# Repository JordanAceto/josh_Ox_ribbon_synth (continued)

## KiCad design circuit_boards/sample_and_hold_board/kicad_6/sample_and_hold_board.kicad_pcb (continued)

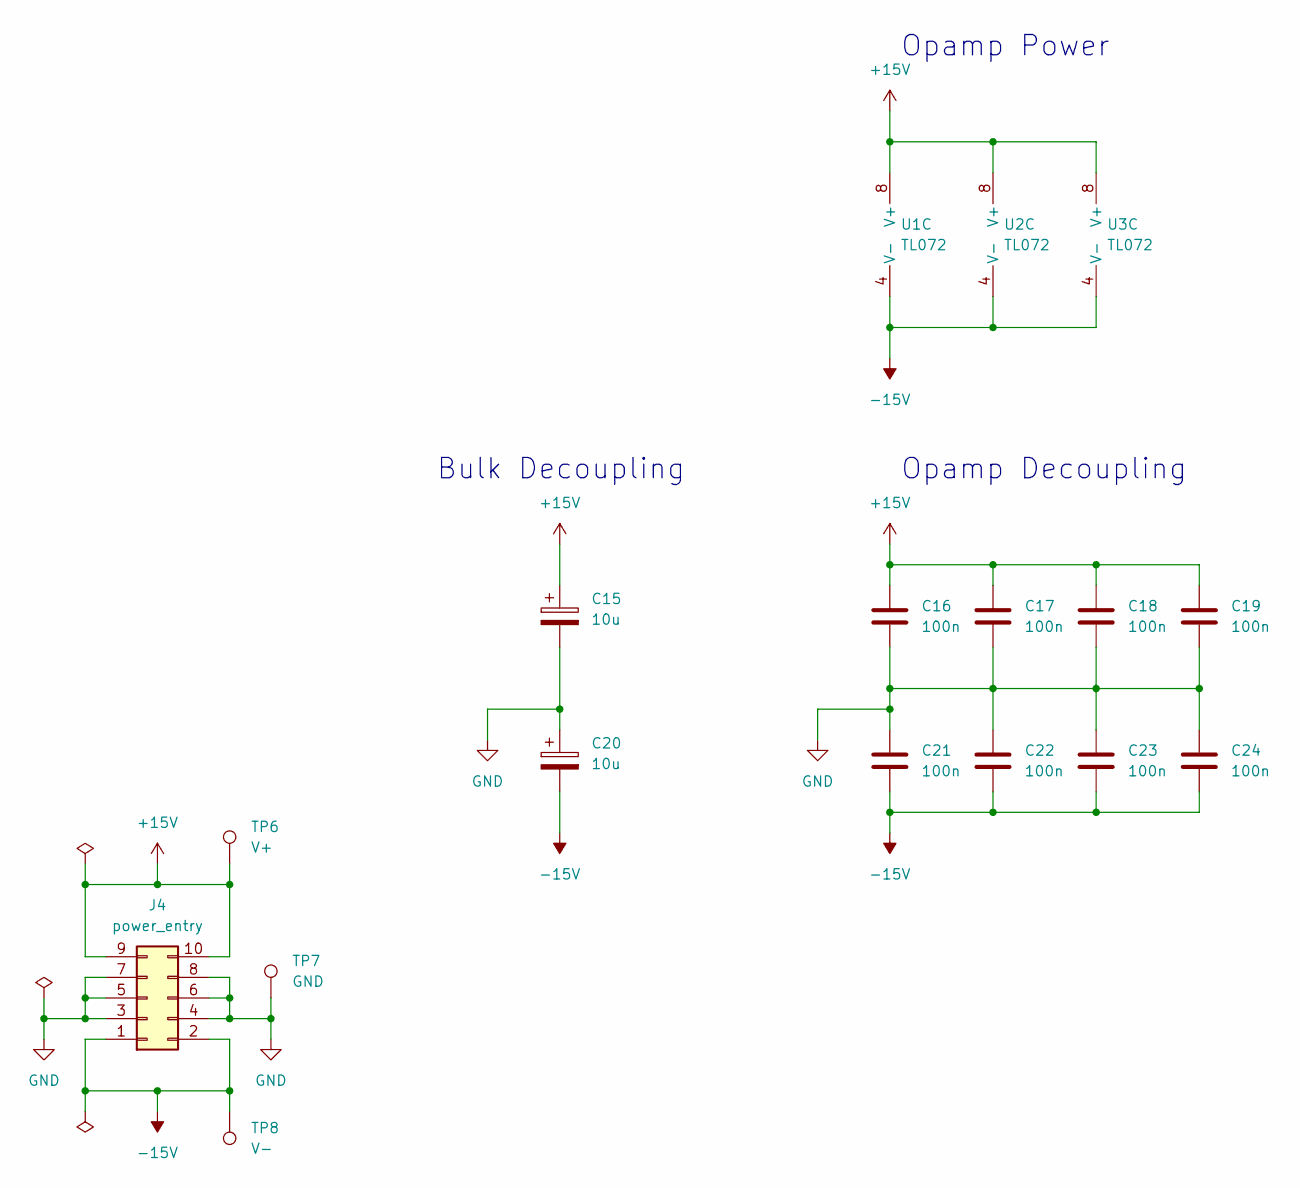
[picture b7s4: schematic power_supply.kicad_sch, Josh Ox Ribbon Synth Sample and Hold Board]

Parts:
C15, C20: 10u; CP_Radial_D6.3mm_P2.50mm
C16, C17, C18, C19, C21, C22, C23, C24: 100n; C_0805_2012Metric
J4: power_entry; IDC-Header_2x05_P2.54mm_Vertical
TP6: V+; TestPoint_Keystone_5000-5004_Miniature
TP7: GND; TestPoint_Bridge_Pitch7.62mm_Drill1.3mm
TP8: V-; TestPoint_Keystone_5000-5004_Miniature
U1, U2, U3: TL072; SO-8_5.3x6.2mm_P1.27mm

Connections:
+15V: C15.1, C16.1, C17.1, C18.1, C19.1, J4.9, J4.10, TP6.1, U1.8 (V+), U2.8 (V+), U3.8 (V+); also elsewhere on the board
-15V: C20.2, C21.2, C22.2, C23.2, C24.2, J4.1, J4.2, TP8.1, U1.4 (V-), U2.4 (V-), U3.4 (V-); also elsewhere on the board
GND: C15.2, C16.2, C17.2, C18.2, C19.2, C20.1, C21.1, C22.1, C23.1, C24.1, J4.3, J4.4, J4.5, J4.6, J4.7, J4.8, TP7.1; also elsewhere on the board

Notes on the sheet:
Opamp Decoupling
Opamp Power
Bulk Decoupling

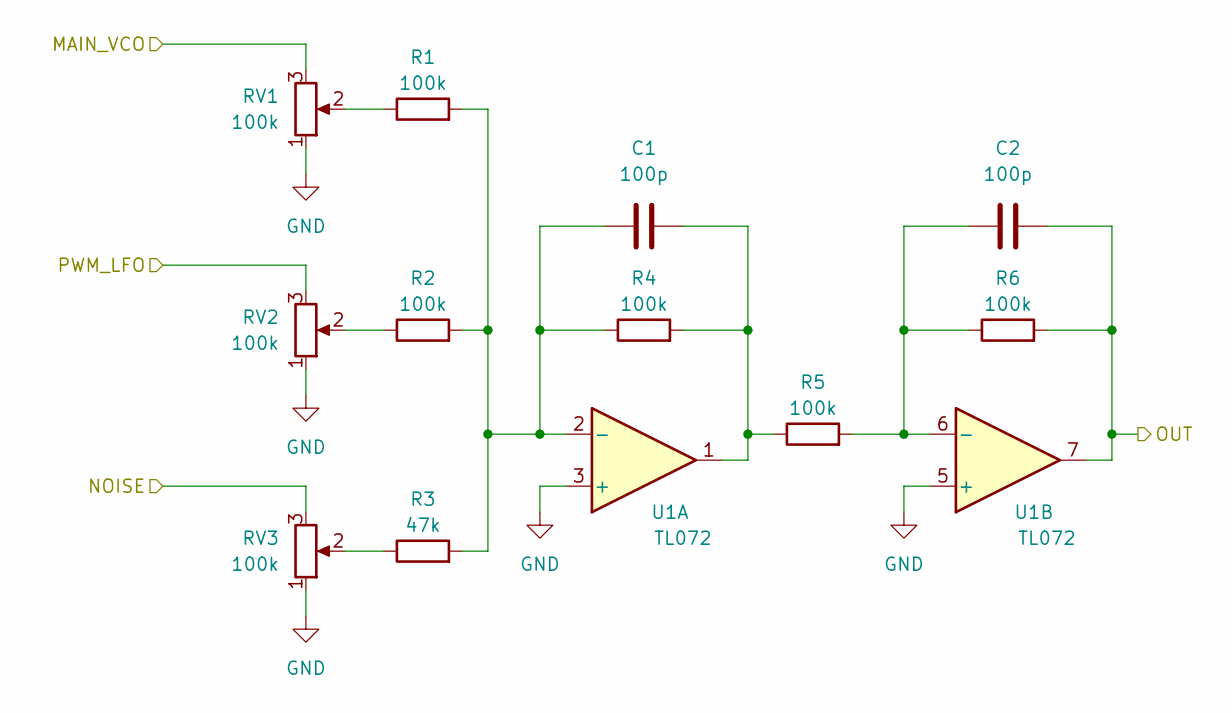
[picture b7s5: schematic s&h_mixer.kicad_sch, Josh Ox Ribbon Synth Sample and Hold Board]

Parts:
C1, C2: 100p; C_0805_2012Metric
R1, R2, R4, R5, R6: 100k; R_0805_2012Metric
R3: 47k; R_0805_2012Metric
RV1, RV2, RV3: 100k; Potentiometer_Alpha_RD901F-40-00D_Single_Vertical
U1: TL072; SO-8_5.3x6.2mm_P1.27mm

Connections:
/S&H_MIXER: C2.2, R6.2, U1.7; also elsewhere on the board
/noise_generator/NOISE_OUT: RV3.3; also elsewhere on the board
/s&h_mixer/MAIN_VCO: RV1.3; also elsewhere on the board
/s&h_mixer/PWM_LFO: RV2.3; also elsewhere on the board
GND: RV1.1, RV2.1, RV3.1, U1.3 (+), U1.5 (+); also elsewhere on the board
unnamed: C1.1, R1.2, R2.2, R3.2, R4.1, U1.2 (-)
unnamed: C1.2, R4.2, R5.1, U1.1
unnamed: C2.1, R5.2, R6.1, U1.6 (-)
unnamed: R1.1, RV1.2
unnamed: R2.1, RV2.2
unnamed: R3.1, RV3.2

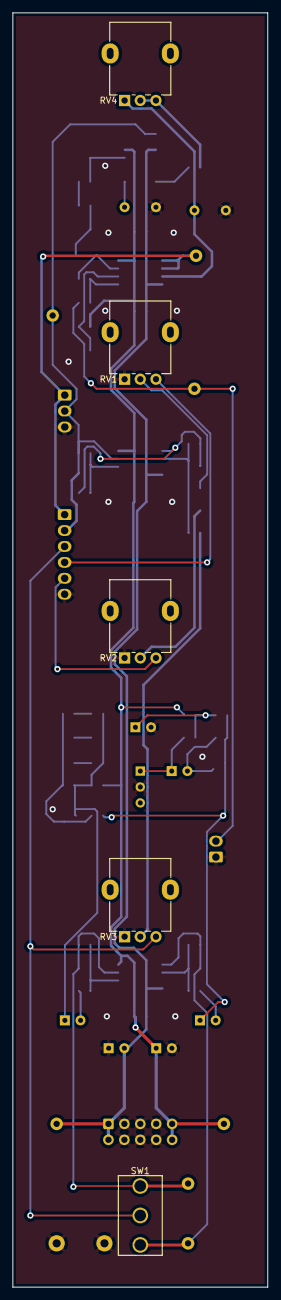
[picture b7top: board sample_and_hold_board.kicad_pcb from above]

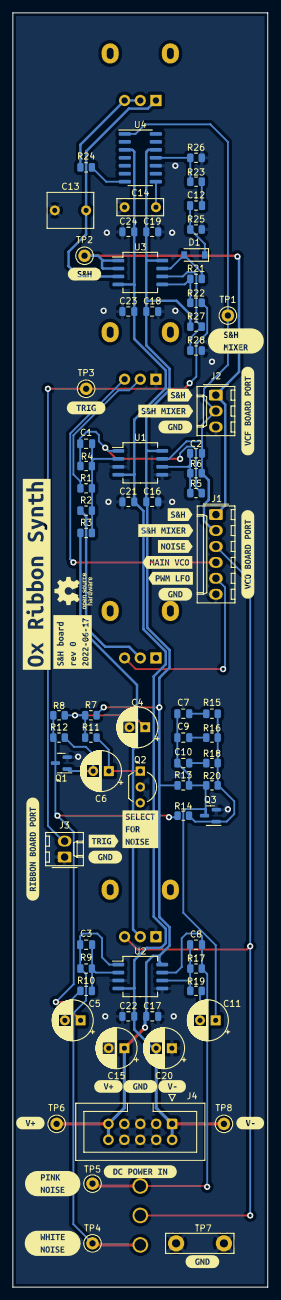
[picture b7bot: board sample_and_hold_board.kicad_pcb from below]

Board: 2 copper layers, 40.6 x 203.2 mm, 106 parts (101 on the bottom side), 40 nets.

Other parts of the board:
kibuzzard-62AC7A9F: G***; kibuzzard-62AC7A9F
kibuzzard-62AC78CB: G***; kibuzzard-62AC78CB
kibuzzard-62AC81C6: G***; kibuzzard-62AC81C6
kibuzzard-62AC81E3: G***; kibuzzard-62AC81E3
kibuzzard-62AC82BB: G***; kibuzzard-62AC82BB
kibuzzard-62AC82DF: G***; kibuzzard-62AC82DF
kibuzzard-62AC755C, kibuzzard-62AC755C#2, kibuzzard-62AC755C#3, kibuzzard-62AC755C#4, kibuzzard-62AC755C#5: G***; kibuzzard-62AC755C
kibuzzard-62AC791A, kibuzzard-62AC791A#2: G***; kibuzzard-62AC791A
kibuzzard-62AC792A, kibuzzard-62AC792A#2: G***; kibuzzard-62AC792A
kibuzzard-62AC813F, kibuzzard-62AC813F#2: G***; kibuzzard-62AC813F
kibuzzard-62AC818C: G***; kibuzzard-62AC818C
kibuzzard-62AC819F: G***; kibuzzard-62AC819F
kibuzzard-62AC822A: G***; kibuzzard-62AC822A
kibuzzard-62AC8121: G***; kibuzzard-62AC8121
kibuzzard-62AC8151, kibuzzard-62AC8151#2: G***; kibuzzard-62AC8151
kibuzzard-62AC8170: G***; kibuzzard-62AC8170
kibuzzard-62AC8211: G***; kibuzzard-62AC8211
kibuzzard-62AC8240: G***; kibuzzard-62AC8240
kibuzzard-62AC8254: G***; kibuzzard-62AC8254
kibuzzard-62AC8271: G***; kibuzzard-62AC8271
kibuzzard-62AC8282: G***; kibuzzard-62AC8282
